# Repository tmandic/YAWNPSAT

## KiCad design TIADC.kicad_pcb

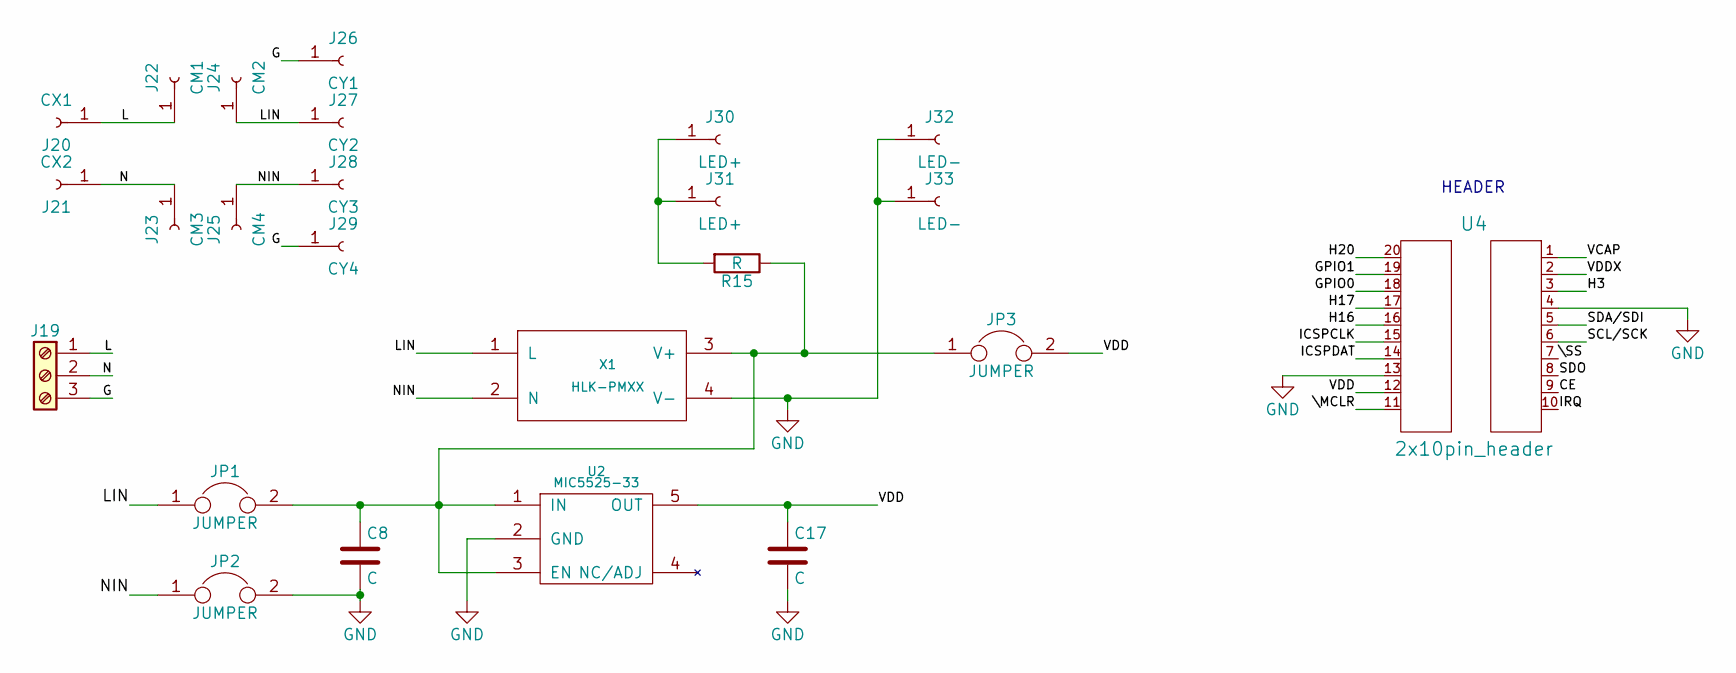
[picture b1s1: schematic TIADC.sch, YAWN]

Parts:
C8, C17: C; 0805
J19: Screw_Terminal_01x03; TerminalBlock_bornier-3_P5.08mm
J20: CX1; 3mm_1mm
J21: CX2; 3mm_1mm
J22: CM1; 3mm_1mm
J23: CM3; 3mm_1mm
J24: CM2; 3mm_1mm
J25: CM4; 3mm_1mm
J26: CY1; 3mm_1mm
J27: CY2; 3mm_1mm
J28: CY3; 3mm_1mm
J29: CY4; 3mm_1mm
J30, J31: LED+; 3mm_1mm
J32, J33: LED-; 3mm_1mm
JP1, JP2: JUMPER; R_Axial_DIN0204_L3.6mm_D1.6mm_P5.08mm_Horizontal
JP3: JUMPER; J1x04
R15: R; R_Axial_DIN0207_L6.3mm_D2.5mm_P10.16mm_Horizontal
U2: MIC5525-33; SOT-23-5DDC
U4: 2x10pin_header; HEADER; Farnell 1667516
X1: HLK-PMXX; HLK-PM03

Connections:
/CE: U4.9
/G: J19.3, J26.1, J29.1
/GPIO0: U4.18
/GPIO1: U4.19
/H3: U4.3
/H16: U4.16
/H17: U4.17
/H20: U4.20
/ICSPCLK: U4.15
/ICSPDAT: U4.14
/IRQ: U4.10
/L: J19.1, J20.1, J22.1
/LIN: J24.1, J27.1, JP1.1, X1.1 (L)
/N: J19.2, J21.1, J23.1
/NIN: J25.1, J28.1, JP2.1, X1.2 (N)
/SCL/SCK: U4.6
/SDA/SDI: U4.5
/SDO: U4.8
/VCAP: U4.1
/VDD: C17.1, JP3.2, U2.5 (OUT), U4.12
/VDDX: U4.2
/\MCLR: U4.11
/\SS: U4.7
GND: C8.2, C17.2, J32.1, J33.1, JP2.2, U2.2 (GND), U4.4, U4.13, X1.4 (V-)
unnamed: C8.1, JP1.2, JP3.1, R15.1, U2.1 (IN), U2.3 (EN), X1.3 (V+)
unnamed: J30.1, J31.1, R15.2

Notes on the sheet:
HEADER

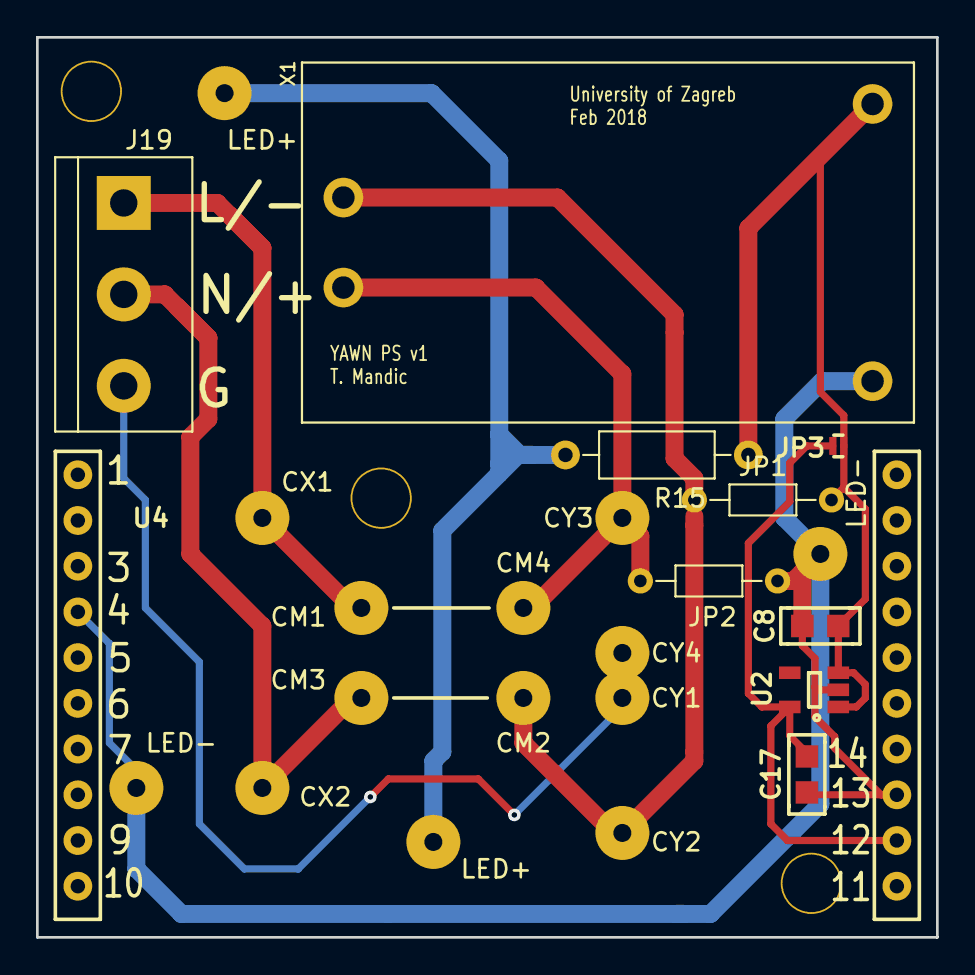
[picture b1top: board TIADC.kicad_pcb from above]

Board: 2 copper layers, 50.0 x 50.0 mm, 24 parts (0 on the bottom side), 9 nets.
